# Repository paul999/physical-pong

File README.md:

# physical-pong

Do you remember pong from a long time ago? Well, I did, and I decided to make a physical version of the game.

This is the code required to run on the arduino mega. You can find more information about this project on the site: www.physical-pong.com

# Installing

This code is written for a arduino mega. You will need the platformio editor if you want to have it work out of the box.
It won't work with the default arduino IDE out of the box, and this is not something I plan on supporting.

If you are using this code without the ramps board as suggested, please make sure to check the pins in config.h, otherwise it won't work. For instructions on how to use the default configuration, please read the information found at https://www.physical-pong.com/instructions/
In config.php you can also enable DEBUG mode, which does write debug statements into the Serial console for debugging. It is suggested to disable this if you don't need it.

Before compiling, make sure you set the correct processor in paltformio.ini, otherwise you won't be able to upload your code to your Arduino.

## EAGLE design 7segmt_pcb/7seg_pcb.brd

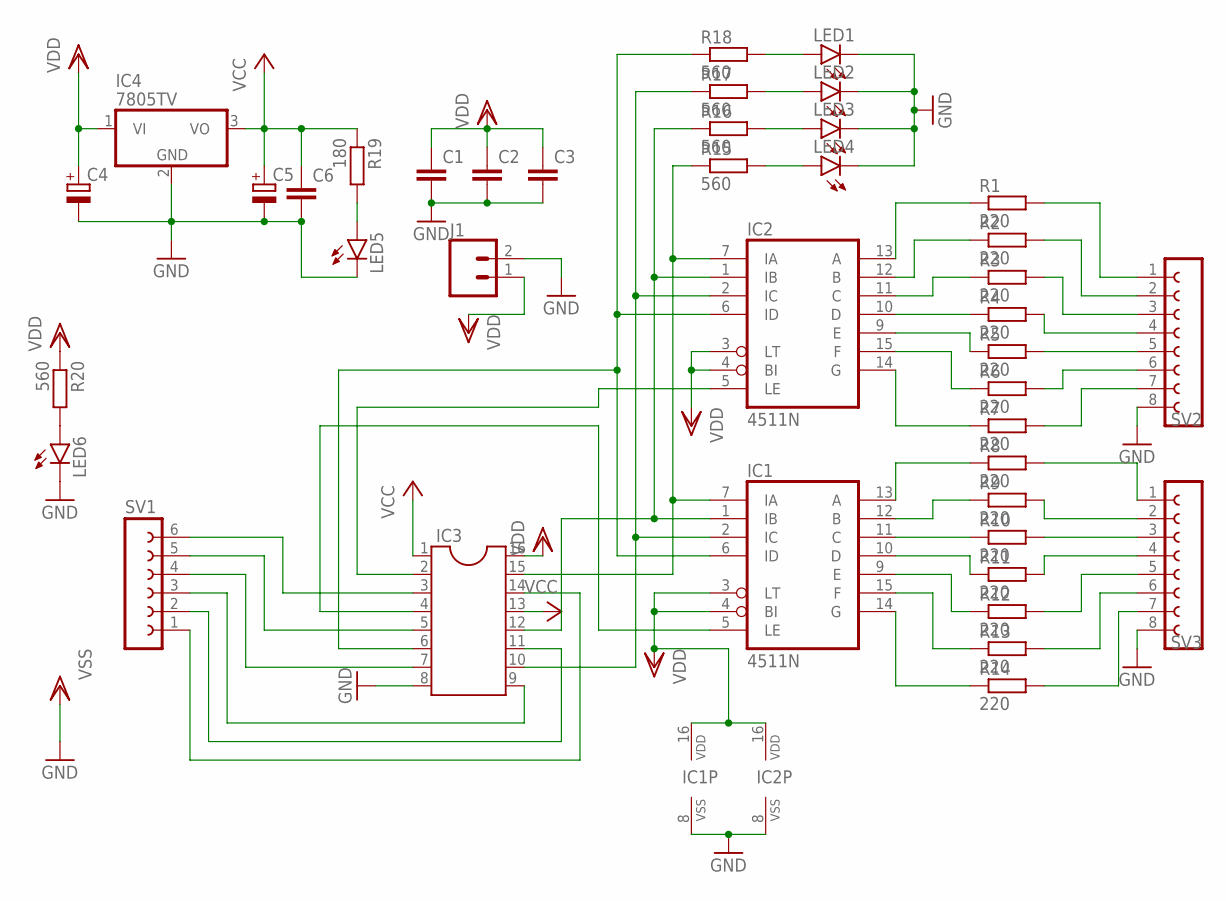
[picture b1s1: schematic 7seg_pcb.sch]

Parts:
C1, C2, C3, C6: C-EUC0805K; C0805K
C4, C5: CPOL-EUD; PANASONIC_D
IC1, IC2: 4511N; DIL16
IC3: DIL16S; SOCKET-16
IC4: 7805TV; TO220V
J1: CONN_025MM; SCREWTERMINAL-5MM-2
LED1, LED2, LED3, LED4, LED5, LED6: LEDCHIPLED_0805; CHIPLED_0805
R1, R2, R3, R4, R5, R6, R7, R8, R9, R10, R11, R12, R13, R14: 220; R0805
R15, R16, R17, R18, R20: 560; R0805
R19: 180; R0805
SV1: FE06-1; FE06
SV2, SV3: FE08-1; FE08

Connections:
GND: C1.2, C2.2, C3.2, C4.-, C5.-, C6.2, IC1.8 (VSS), IC2.8 (VSS), IC3.8, IC4.2 (GND), J1.2, LED1.C, LED2.C, LED3.C, LED4.C, LED5.C, LED6.C, SV2.8, SV3.8
unnamed: IC2.13 (A), R1.1
unnamed: IC2.12 (B), R2.1
unnamed: IC2.11 (C), R3.1
unnamed: IC2.10 (D), R4.1
unnamed: R14.2, SV3.7
unnamed: R13.2, SV3.6
unnamed: R12.2, SV3.5
unnamed: R11.2, SV3.4
unnamed: R10.2, SV3.3
unnamed: R9.2, SV3.2
unnamed: R8.2, SV3.1
unnamed: R7.2, SV2.7
unnamed: R6.2, SV2.6
unnamed: R5.2, SV2.5
unnamed: R4.2, SV2.4
unnamed: R3.2, SV2.3
unnamed: R2.2, SV2.2
unnamed: R1.2, SV2.1
unnamed: IC2.9 (E), R5.1
unnamed: IC2.15 (F), R6.1
unnamed: IC2.14 (G), R7.1
unnamed: IC1.13 (A), R8.1
unnamed: IC1.12 (B), R9.1
unnamed: IC1.11 (C), R10.1
unnamed: IC1.10 (D), R11.1
unnamed: IC1.9 (E), R12.1
unnamed: IC1.15 (F), R13.1
unnamed: IC1.14 (G), R14.1
unnamed: IC1.7 (IA), IC2.7 (IA), IC3.15, R15.1
unnamed: LED1.A, R18.2
unnamed: IC1.1 (IB), IC2.1 (IB), IC3.12, R16.1
unnamed: LED2.A, R17.2
unnamed: IC1.2 (IC), IC2.2 (IC), IC3.10, R17.1
unnamed: IC1.6 (ID), IC2.6 (ID), IC3.6, R18.1
unnamed: IC1.5 (LE), IC3.4
unnamed: IC3.3, SV1.6
unnamed: LED3.A, R16.2
unnamed: LED4.A, R15.2
unnamed: IC3.14, SV1.1
unnamed: IC3.11, SV1.2
unnamed: IC3.9, SV1.3
unnamed: IC3.7, SV1.4
unnamed: IC3.5, SV1.5
unnamed: LED5.A, R19.2
unnamed: IC2.5 (LE), IC3.2
unnamed: LED6.A, R20.2
VCC: C5.+, C6.1, IC3.1, IC3.13, IC4.3 (VO), R19.1
VDD: C1.1, C2.1, C3.1, C4.+, IC1.3 (LT), IC1.4 (BI), IC1.16 (VDD), IC2.3 (LT), IC2.4 (BI), IC2.16 (VDD), IC3.16, IC4.1 (VI), J1.1, R20.1

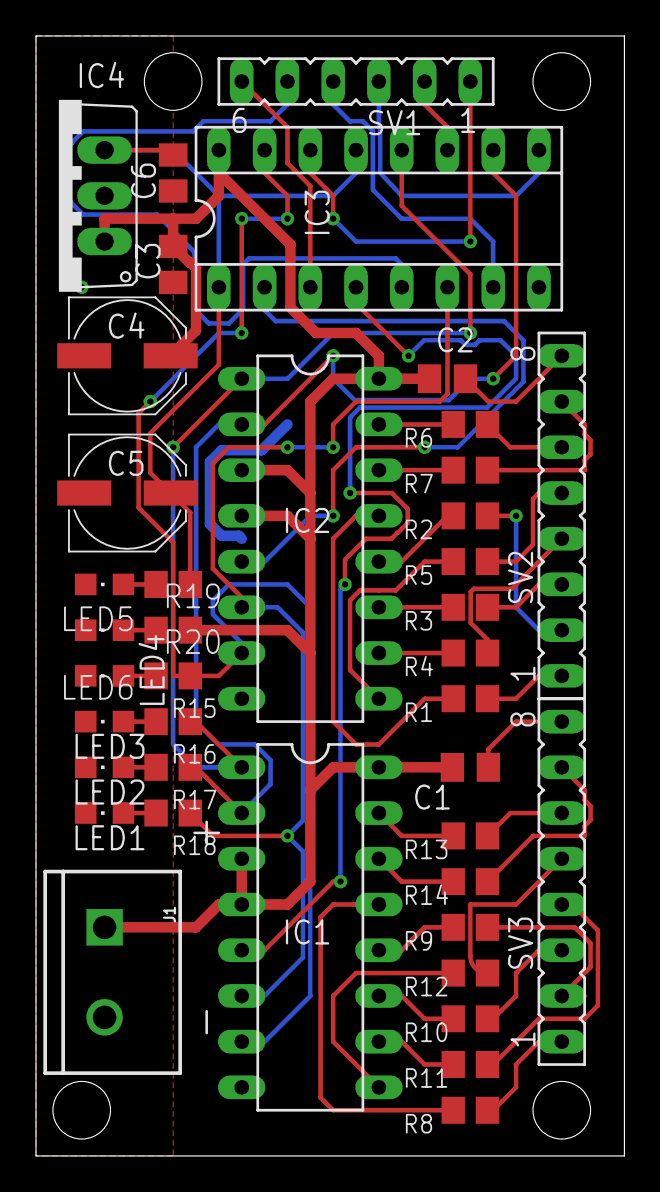
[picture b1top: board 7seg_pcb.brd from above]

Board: 2 copper layers, 32.7 x 62.2 mm, 40 parts (0 on the bottom side), 49 nets.

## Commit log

2019-01-19 Add basic files for arduino code
2019-01-27 Lots of android code to get started
2019-01-27 Add readme text
2019-01-27 first configuration for ramps
2019-01-27 Configuration updates in code as well
2019-02-06 Getting things started. Lots of fixes for motor control and stuff like that.
2019-02-06 Testing more of the startup process :D
2019-02-06 Remove return & change timeout to make it a bit slower.
2019-02-06 Add some more
2019-02-06 Remove files
2019-02-06 Add start of the game code.
2019-02-17 Do not go to the center on init (As we will do the home/center thingie again later) Change pins around for usage. Some other misc cleanup.
2019-02-17 Rewrite some of the moving logic to do multiple stuff at the same time.
2019-02-22 Remove continues logging. It makes the arduino really slow. Change timings between movements. Set correct location pin
2019-02-23 Lot of changes to the code. Rewrite the way endstops and stuff are handled. Currently need to redo some of the stepper motor stuff, as due to the timer changing, it is now sort of borked (But it stil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
2019-02-24 Fixing a issue with pin init not working. Make sure to limit left/right buttons for players correctly. Some more cleanup
2019-02-24 Refactor some stuff around. Setup code for hit checks for end of game.
2019-03-23 Bunch of changes regarding the game. Please note that the dead/alive calculation is broken atm.
2019-03-23 Rewrite player is dead control stuff. Should be working now okayish enough for now. Also cleaned up config a bit.
2019-05-19 Add support for 7 segment scoring display. Requires a bit of setup in config.h and enabling it before it works. Requires a seperate PCB the bitshifter and stuff. More info on it soon.
    Change the speed of the game a bit.
2019-05-19 Add 7 segment PCB
2019-06-16 Add support for 4 LED strips (Twe side and one for each player).
2019-06-16 Use the LED strips for some error handling.

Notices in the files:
7segmt_pcb/7seg_pcb.brd:
(C) 2019 By Paul Sohier.
parts and their libraries:
SparkFun-Connectors: Licensing: Creative Commons ShareAlike 4.0 International - https://creativecommons.org/licenses/by-sa/4.0
